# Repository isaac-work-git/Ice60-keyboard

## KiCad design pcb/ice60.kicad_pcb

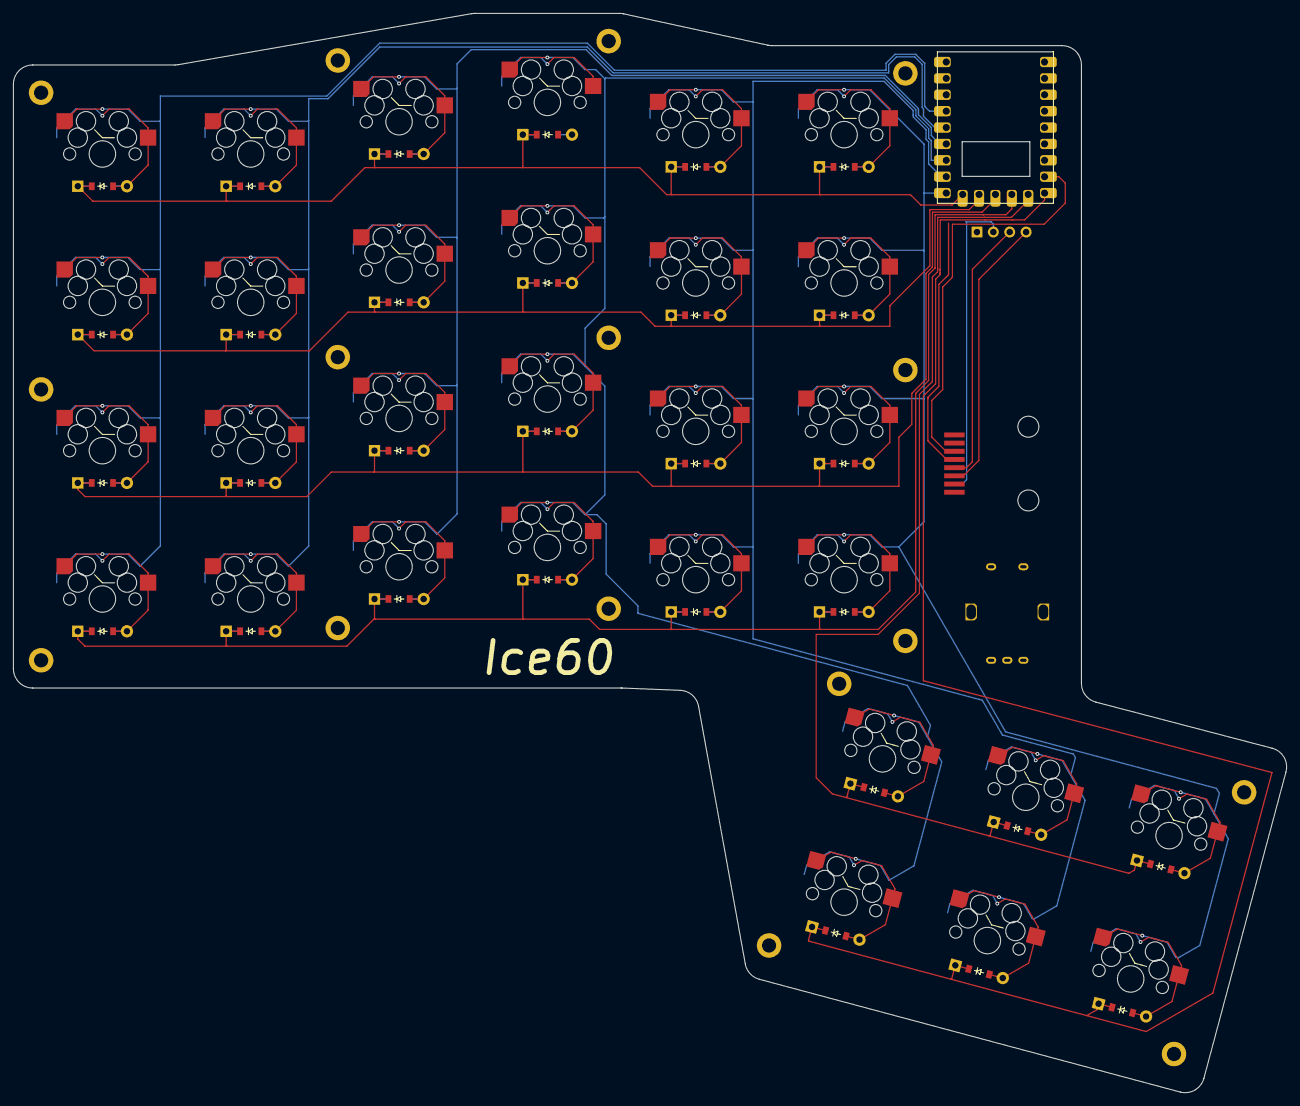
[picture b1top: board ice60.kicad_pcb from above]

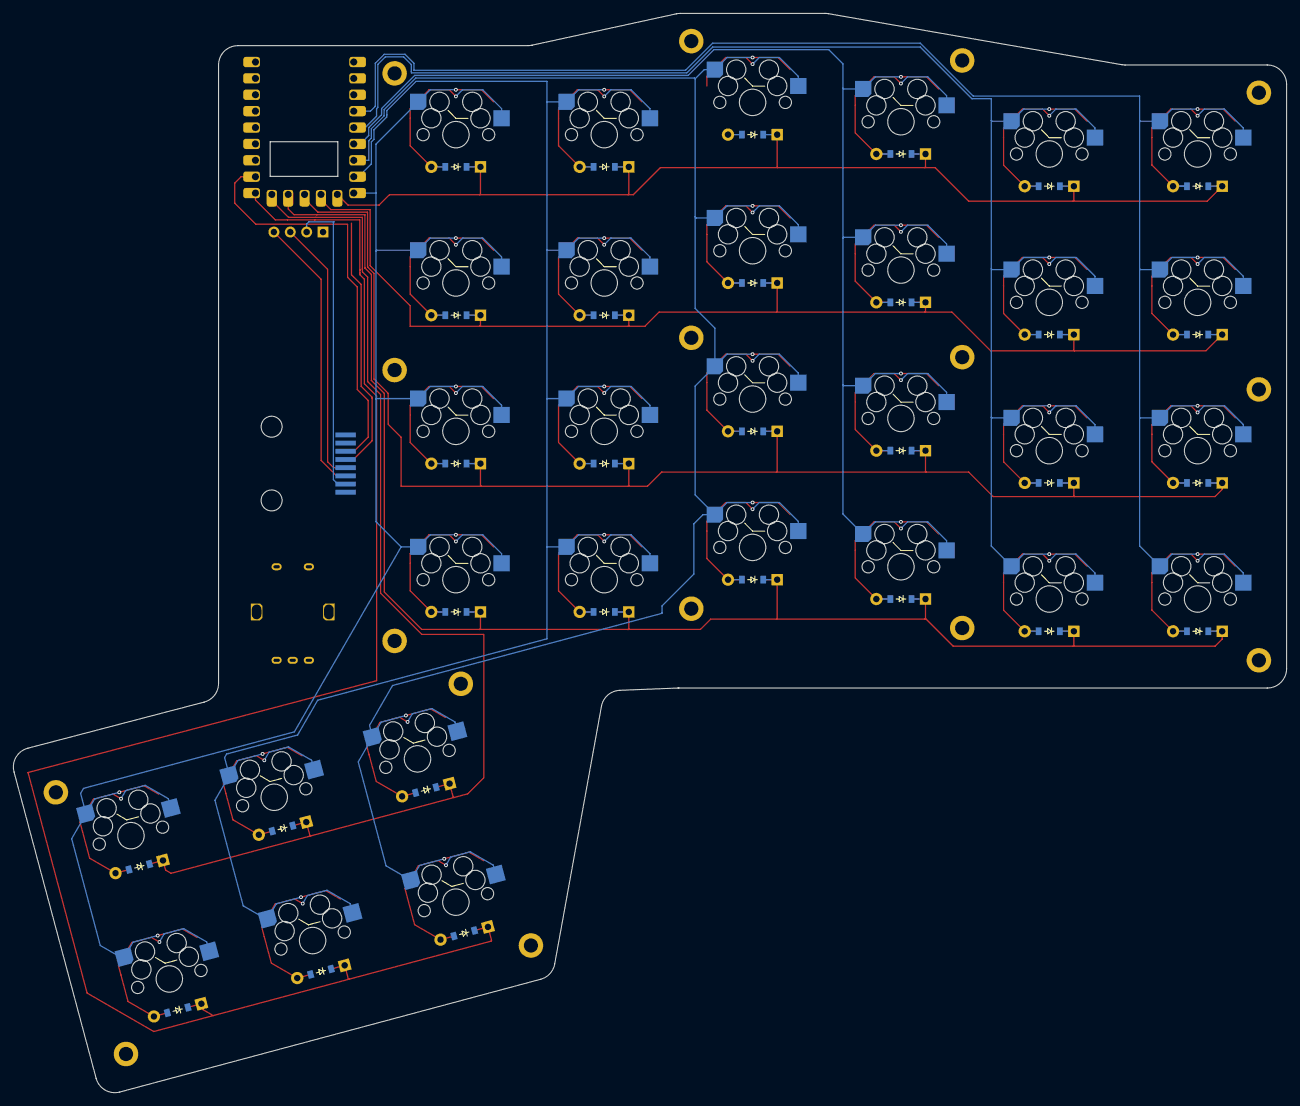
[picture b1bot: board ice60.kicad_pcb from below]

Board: 2 copper layers, 197.4 x 167.3 mm, 80 parts (30 on the bottom side), 52 nets.

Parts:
D1, D2, D3, D4, D5, D6, D7, D8, D9, D10, D11, D12, D13, D14, D15, D16, D17, D18, D19, D20, D21, D22, D23, D24, D25, D26, D27, D28, D29, D30: diode_tht_sod123
H1, H2, H3, H4, H5, H6, H7, H8, H9, H10, H11, H12, H13, H14, H15, H16: mounting_hole_plated
J1: RJ45_8P8C; rj45_8p8c_smt_reversible
OLED1: OLED; OLED_headers
RE1: rotary_encoder_ec11_ec12
RP2040Zero1: RP2040-Zero
S1, S2, S3, S4, S5, S6, S7, S8, S9, S10, S11, S12, S13, S14, S15, S16, S17, S18, S19, S20, S21, S22, S23, S24, S25, S26, S27, S28, S29, S30: switch_mx

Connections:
C1: RP2040Zero1.23, S1.2, S2.2, S3.2, S4.2
C2: RP2040Zero1.22, S5.2, S6.2, S7.2, S8.2
C3: RP2040Zero1.18, S9.2, S10.2, S11.2, S12.2
C4: RP2040Zero1.17, S13.2, S14.2, S15.2, S16.2, S25.2, S26.2
C5: RP2040Zero1.16, S17.2, S18.2, S19.2, S20.2, S27.2, S28.2
C6: RP2040Zero1.15, S21.2, S22.2, S23.2, S24.2, S29.2, S30.2
DETECT: J1.6, RP2040Zero1.8
ENC_A: RE1.A, RP2040Zero1.5
ENC_B: RE1.B, RP2040Zero1.6
ENC_SW: RE1.S1, RP2040Zero1.2
GND: J1.1, OLED1.1, RE1.S2, RP2040Zero1.20
NC: J1.7, J1.8, RP2040Zero1.1, RP2040Zero1.21
R1: D4.1, D8.1, D12.1, D16.1, D20.1, D24.1, RP2040Zero1.14
R2: D3.1, D7.1, D11.1, D15.1, D19.1, D23.1, RP2040Zero1.13
R3: D2.1, D6.1, D10.1, D14.1, D18.1, D22.1, RP2040Zero1.12
R4: D1.1, D5.1, D9.1, D13.1, D17.1, D21.1, RP2040Zero1.11
R5: D26.1, D28.1, D30.1, RP2040Zero1.10
R6: D25.1, D27.1, D29.1, RP2040Zero1.9
RST: J1.5, RP2040Zero1.7
SCL: J1.4, OLED1.3, RP2040Zero1.4
SDA: J1.3, OLED1.4, RP2040Zero1.3
VCC: J1.2, OLED1.2, RP2040Zero1.19
index_bottom: D17.2, S17.1
index_home: D18.2, S18.1
index_num: D20.2, S20.1
index_top: D19.2, S19.1
inner_bottom: D21.2, S21.1
inner_home: D22.2, S22.1
inner_num: D24.2, S24.1
inner_top: D23.2, S23.1
insidett_bottom: D25.2, S25.1
insidett_top: D26.2, S26.1
middle_bottom: D13.2, S13.1
middle_home: D14.2, S14.1
middle_num: D16.2, S16.1
middle_top: D15.2, S15.1
midtt_bottom: D27.2, S27.1
midtt_top: D28.2, S28.1
outer_bottom: D1.2, S1.1
outer_home: D2.2, S2.1
outer_num: D4.2, S4.1
outer_top: D3.2, S3.1
outt_bottom: D29.2, S29.1
outt_top: D30.2, S30.1
pinky_bottom: D5.2, S5.1
pinky_home: D6.2, S6.1
pinky_num: D8.2, S8.1
pinky_top: D7.2, S7.1
ring_bottom: D9.2, S9.1
ring_home: D10.2, S10.1
ring_num: D12.2, S12.1
ring_top: D11.2, S11.1

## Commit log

2026-03-20 This is the repo for the Ice 60 keyboard
2026-03-20 Adding KiCAD footprint for the Rp 2040 Zero
2026-03-21 Need to confirm rj45, 2040 footprints
2026-03-24 Added rj-45 footprint
2026-03-24 Need to check oled physical size
2026-03-25 Ready for confirmation of net assignment
2026-03-25 Updated a comment for encoder to remember questions
2026-03-26 Updated some nets that are going to be unused. Ready to reviewed.
2026-03-27 Jumpers have been added
2026-03-27 Added jumper text
2026-03-28 Just about ready for routing
2026-03-30 Adding repo to computer
